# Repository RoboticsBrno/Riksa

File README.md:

View this project on [CADLAB.io](https://cadlab.io/project/1114). 

# Riksa
Transport vehicle

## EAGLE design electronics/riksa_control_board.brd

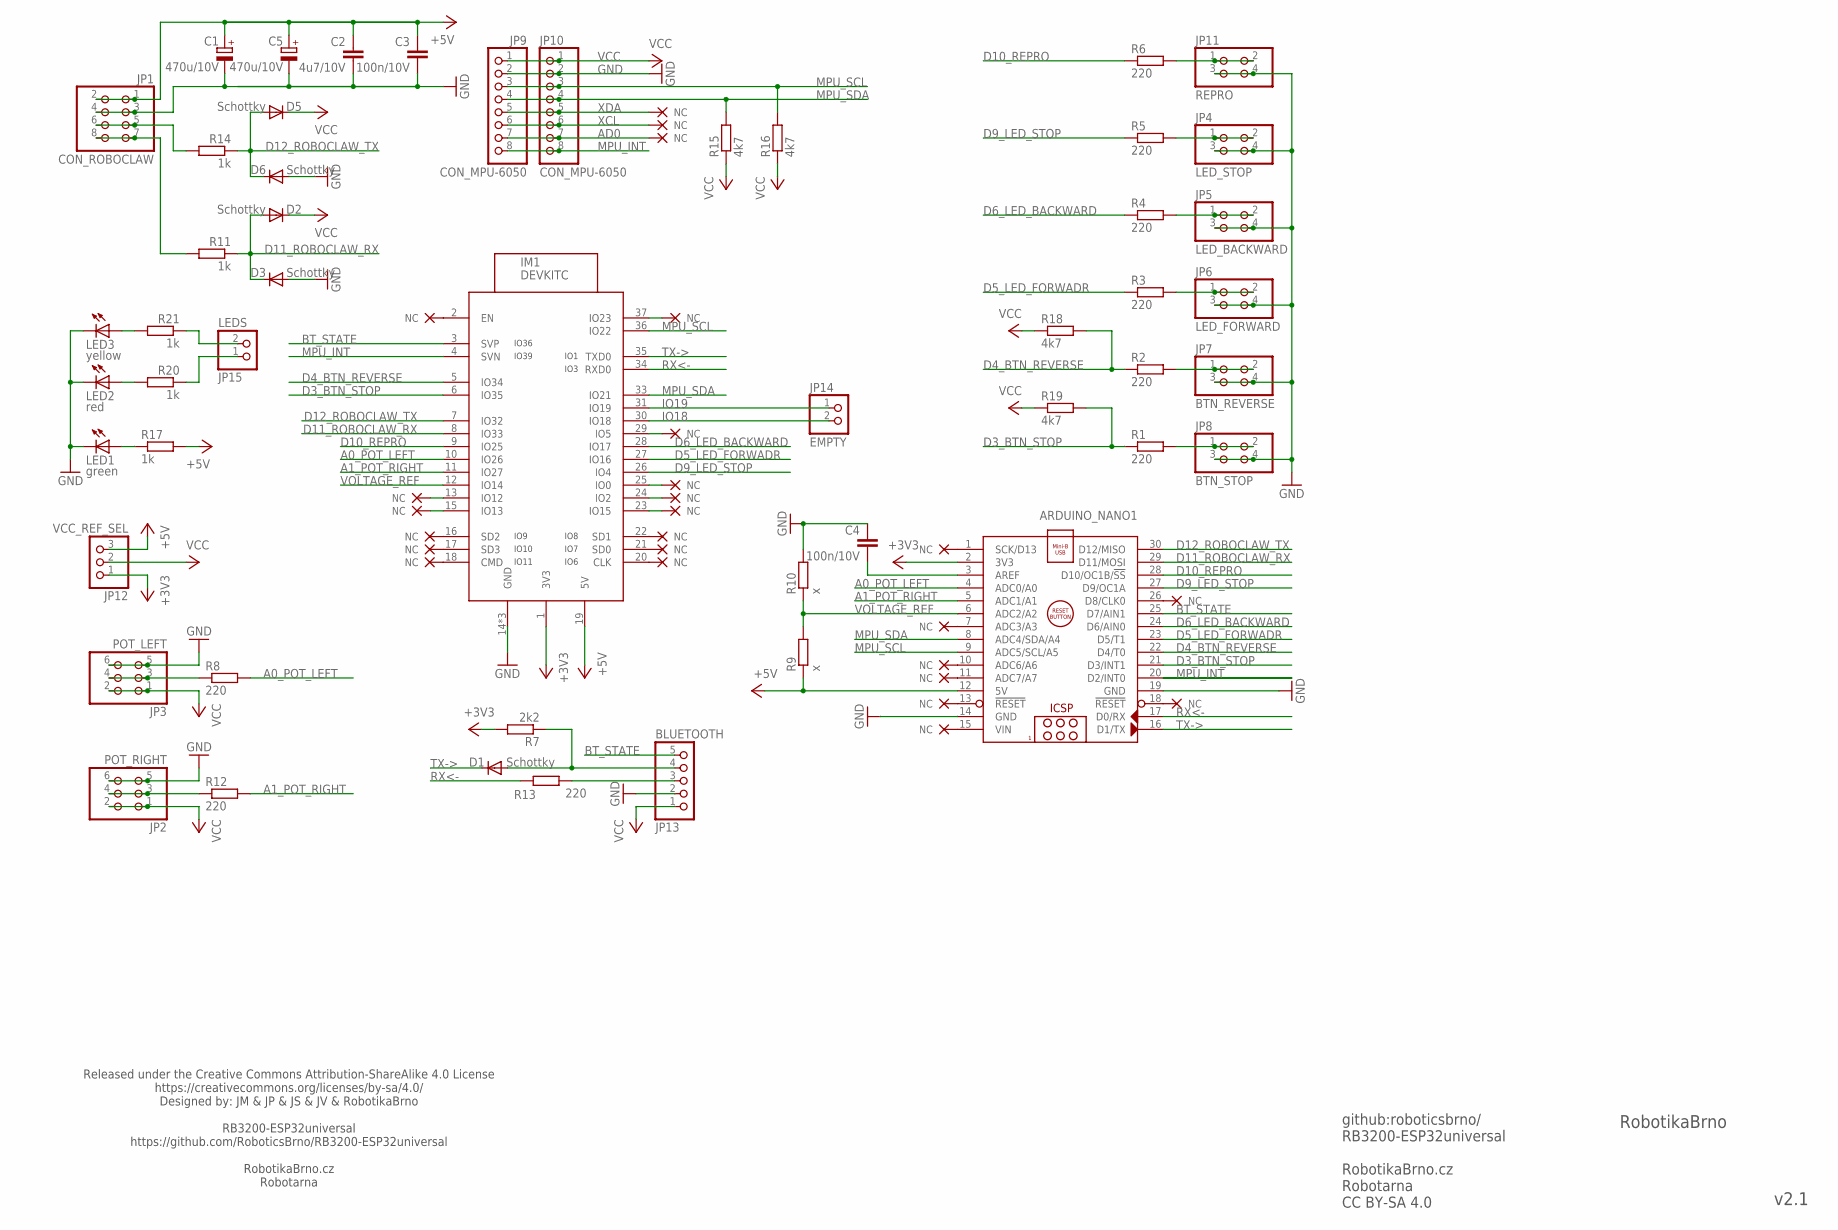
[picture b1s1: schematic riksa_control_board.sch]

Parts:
ARDUINO_NANO1: ARDUINO_NANO
C1, C5: 470u/10V; TT5D6
C2: 4u7/10V; C0805
C3, C4: 100n/10V; C0603
D1, D2, D3, D5, D6: Schottky; D0603
IM1: DEVKITC
JP1: CON_ROBOCLAW; 2X04
JP2: POT_RIGHT; 2X03
JP3: POT_LEFT; 2X03
JP4: LED_STOP; 2X02
JP5: LED_BACKWARD; 2X02
JP6: LED_FORWARD; 2X02
JP7: BTN_REVERSE; 2X02
JP8: BTN_STOP; 2X02
JP9, JP10: CON_MPU-6050; 1X08
JP11: REPRO; 2X02
JP12: VCC_REF_SEL; 1X03
JP13: BLUETOOTH; 1X05/90
JP14: EMPTY; 1X02
JP15: LEDS; 1X02
LED1: green; CHIPLED_0603
LED2: red; CHIPLED_0603
LED3: yellow; CHIPLED_0603
R1, R2, R3, R4, R5, R6, R8, R12, R13: 220; R0805
R7: 2k2; R0805
R9, R10: x; R0805
R11, R14, R17, R20, R21: 1k; R0805
R15, R16, R18, R19: 4k7; R0805

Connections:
+3V3: ARDUINO_NANO1.2 (3V3), IM1.1 (3V3), JP12.1, R7.2
+5V: ARDUINO_NANO1.12 (5V), C1.+, C2.1, C3.1, C5.+, IM1.19 (5V), JP1.1, JP1.2, JP12.3, R9.1, R17.2
A0_POT_LEFT: ARDUINO_NANO1.4 (ADC0/A0), IM1.10 (IO26), R8.2
A0_POT_LEFT_: JP3.3, JP3.4, R8.1
A1_POT_RIGHT: ARDUINO_NANO1.5 (ADC1/A1), IM1.11 (IO27), R12.2
A1_POT_RIGHT_: JP2.3, JP2.4, R12.1
AD0: JP9.7, JP10.7
BT_STATE: ARDUINO_NANO1.25 (D7/AIN1), IM1.3 (SVP), JP13.5
D3_BTN_STOP: ARDUINO_NANO1.21 (D3/INT1), IM1.6 (IO35), R1.1, R19.2
D3_BTN_STOP_: JP8.1, JP8.2, R1.2
D4_BTN_REVERSE: ARDUINO_NANO1.22 (D4/T0), IM1.5 (IO34), R2.1, R18.2
D4_BTN_REVERSE_: JP7.1, JP7.2, R2.2
D5_LED_FORWADR: ARDUINO_NANO1.23 (D5/T1), IM1.27 (IO16), R3.1
D5_LED_FORWADR_: JP6.1, JP6.2, R3.2
D6_LED_BACKWARD: ARDUINO_NANO1.24 (D6/AIN0), IM1.28 (IO17), R4.1
D6_LED_BACKWARD_: JP5.1, JP5.2, R4.2
D9_LED_STOP: ARDUINO_NANO1.27 (D9/OC1A), IM1.26 (IO4), R5.1
D9_LED_STOP_: JP4.1, JP4.2, R5.2
D10_REPRO: ARDUINO_NANO1.28 (D10/OC1B/!SS), IM1.9 (IO25), R6.1
D10_REPRO_: JP11.1, JP11.2, R6.2
D11_ROBOCLAW_RX: ARDUINO_NANO1.29 (D11/MOSI), D2.A, D3.C, IM1.8 (IO33), R11.1
D11_ROBOCLAW_RX_: JP1.7, JP1.8, R11.2
D12_ROBOCLAW_TX: ARDUINO_NANO1.30 (D12/MISO), D5.A, D6.C, IM1.7 (IO32), R14.1
D12_ROBOCLAW_TX_: JP1.5, JP1.6, R14.2
GND: ARDUINO_NANO1.14 (GND), ARDUINO_NANO1.19 (GND), C1.-, C2.2, C3.2, C4.1, C5.-, D3.A, D6.A, IM1.14 (GND), IM1.32 (GND), IM1.38 (GND), JP1.3, JP1.4, JP2.5, JP2.6, JP3.5, JP3.6, JP4.3, JP4.4, JP5.3, JP5.4, JP6.3, JP6.4, JP7.3, JP7.4, JP8.3, JP8.4, JP9.2, JP10.2, JP11.3, JP11.4, JP13.2, LED1.C, LED2.C, LED3.C, R10.2
IO18: IM1.30 (IO18), JP14.2
IO19: IM1.31 (IO19), JP14.1
LED_RED: JP15.1, R20.1
LED_YELLOW: JP15.2, R21.1
MPU_INT: ARDUINO_NANO1.20 (D2/INT0), IM1.4 (SVN), JP9.8, JP10.8
MPU_SCL: ARDUINO_NANO1.9 (ADC5/SCL/A5), IM1.36 (IO22), JP9.3, JP10.3, R16.2
MPU_SDA: ARDUINO_NANO1.8 (ADC4/SDA/A4), IM1.33 (IO21), JP9.4, JP10.4, R15.2
unnamed: LED3.A, R21.2
unnamed: ARDUINO_NANO1.3 (AREF), C4.2
unnamed: LED2.A, R20.2
unnamed: LED1.A, R17.1
RX<-: ARDUINO_NANO1.17 (D0/RX), IM1.34 (RXD0), R13.1
RX<-_: JP13.3, R13.2
TX->: ARDUINO_NANO1.16 (D1/TX), D1.C, IM1.35 (TXD0)
TX->_: D1.A, JP13.4, R7.1
VCC: D2.C, D5.C, JP2.1, JP2.2, JP3.1, JP3.2, JP9.1, JP10.1, JP12.2, JP13.1, R15.1, R16.1, R18.1, R19.1
VOLTAGE_REF: ARDUINO_NANO1.6 (ADC2/A2), IM1.12 (IO14), R9.2, R10.1
XCL: JP9.6, JP10.6
XDA: JP9.5, JP10.5

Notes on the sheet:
github:roboticsbrno/ RB3200-ESP32universal RobotikaBrno.cz Robotarna CC BY-SA 4.0
RobotikaBrno
v2.1
Released under the Creative Commons Attribution-ShareAlike 4.0 License https://creativecommons.org/licenses/by-sa/4.0/ Designed by: JM & JP & JS & JV & RobotikaBrno RB3200-ESP32universal https://github.com/RoboticsBrno/RB3200-ESP32universal RobotikaBrno.cz Robotarna

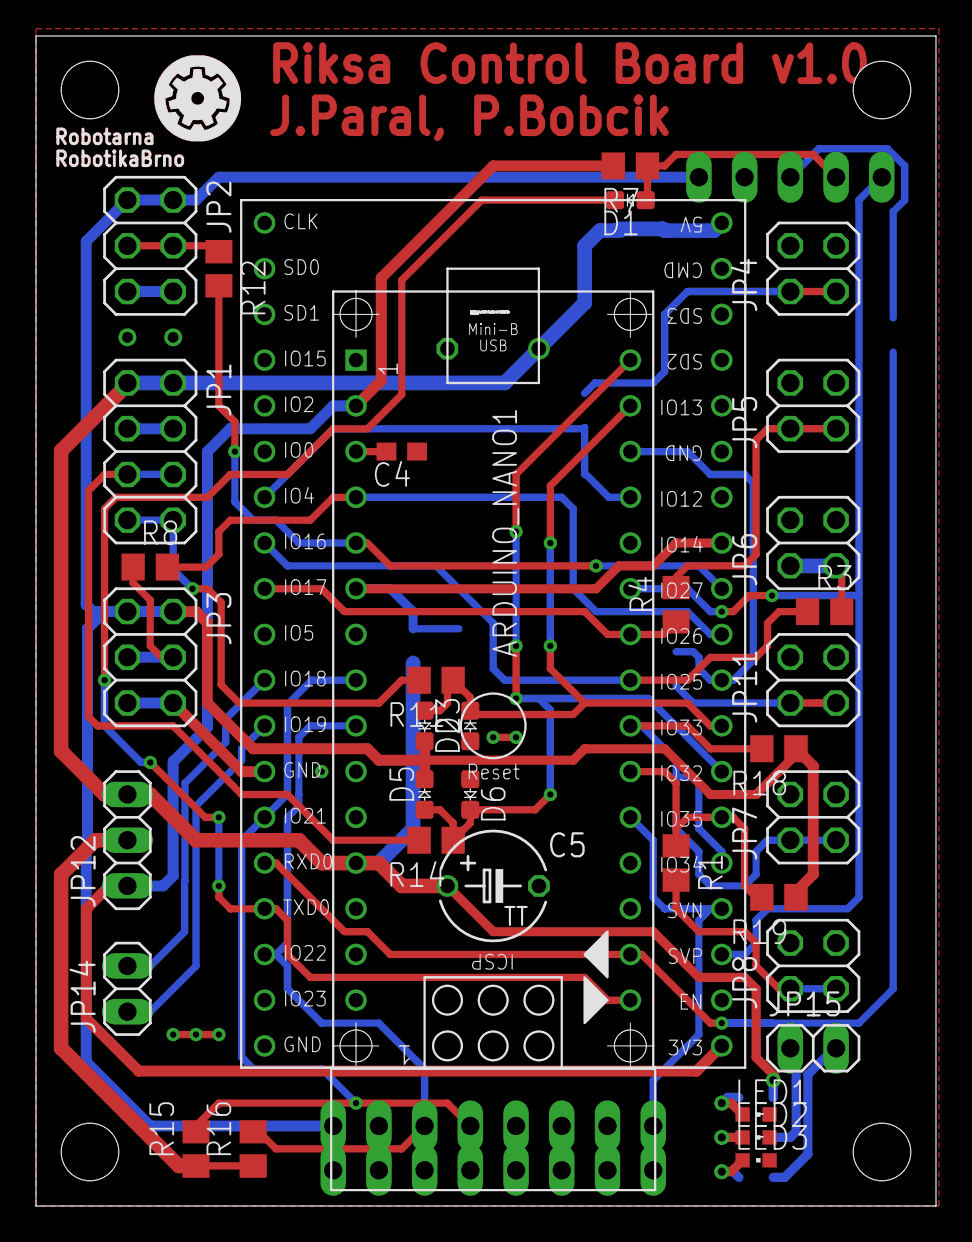
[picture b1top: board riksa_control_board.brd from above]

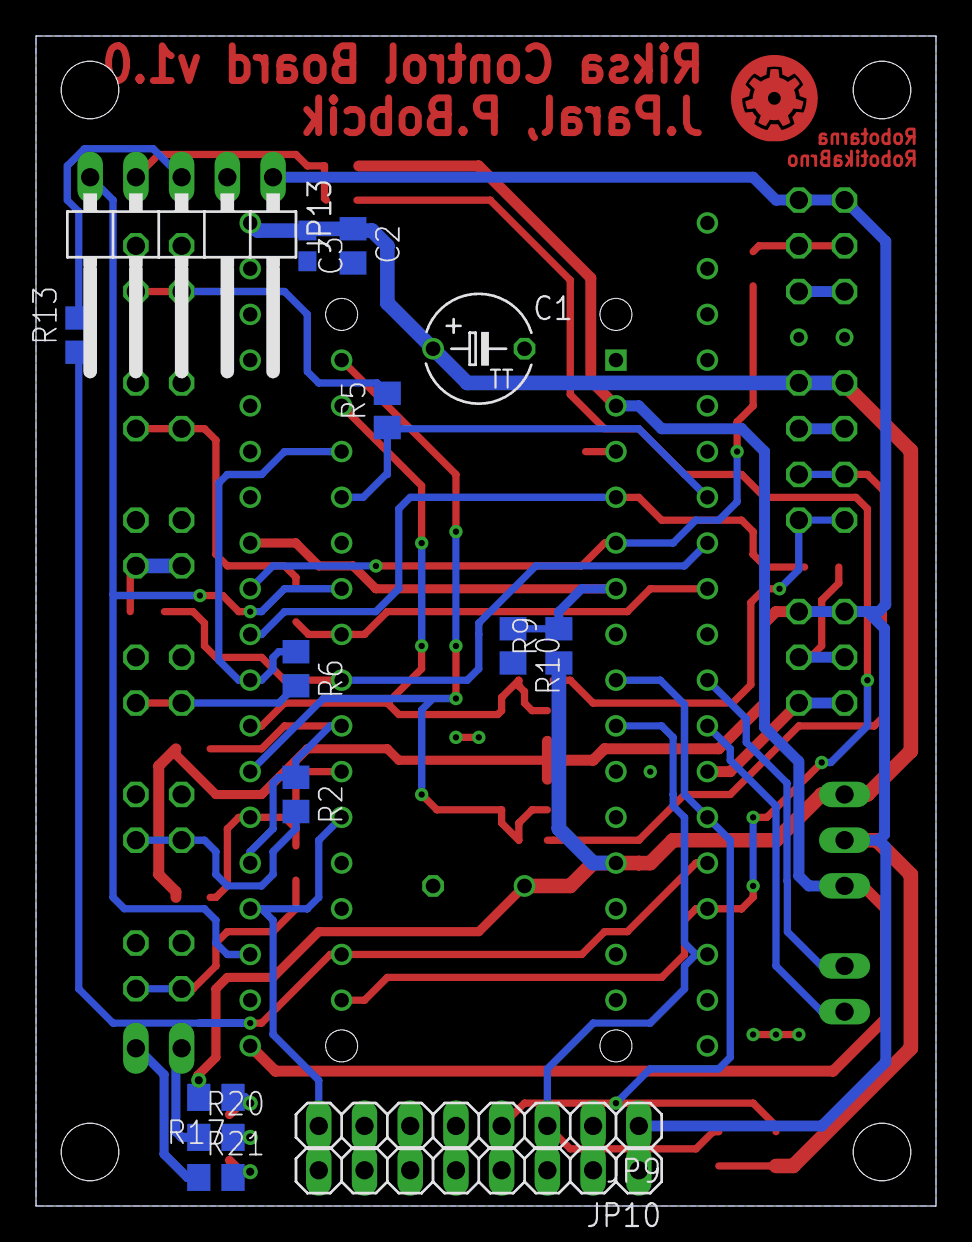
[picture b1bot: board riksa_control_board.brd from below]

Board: 2 copper layers, 50.0 x 65.0 mm, 51 parts (15 on the bottom side), 44 nets.

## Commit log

2018-01-20 ELE+FW: first version of control electronics for Riksa (2017-02-23)
2018-01-20 ELE: new version of control board
2018-01-20 DOC: add photo/video docs
2018-01-20 ELE: add rectangle of size the bluetooth module to board
2018-01-22 ELE: final version of control board
2018-01-23 ELE: fix Kubas comments
2018-01-24 ELE: new layout of board from @PetrBobcik - apply changes in schema from @cednik
2018-01-24 ELE: some improves in layout by @PetrBobcik
2018-01-28 ELE: some improves in layout and schema by @PetrBobcik
2018-02-02 ELE: final version of board
2018-06-01 Backlink to CADLAB.io has been added.

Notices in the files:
parts and their libraries:
esp32: Creative Commons Attribution-ShareAlike 4.0 International
